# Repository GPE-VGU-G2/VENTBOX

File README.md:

# VENTBOX
Official documentation for the ventbox, maintained by Group 2_ GPE PROJECT (VGU_GPE25). This repository contains a technical description, an assembly guide, a Bill of Materials, as well as STEPs and STLs for the 3D printed parts.

VENTBOX is a smart storage solution that helps reduce food waste by actively controlling humidity inside food containers. Its thin, surface-mounted module can be added to existing Lock &amp; Lock lids without affecting the ability to stack containers in the refrigerator.

Ventbox is a module that mounts on the original lid of a 1.9 L Lock & Lock HPL818 food container (the lid only needs two holes, Ø12.3 and Ø10.3). It extracts moist air from the container to limit condensation while the container is kept in the refrigerator.
The module protrudes 8.0 mm above the lid surface and measures 92.8 × 43.3 × 7.5 mm. It is controlled by a Seeed XIAO nRF52840 with an SHT40 sensor; Sunon UB5U3-700 centrifugal blower fan; LP303035 LiPo battery.
Since rev 1.1 there is also a freshness timer: hold the button for 2 s when storing food, and the RGB LED on the module cover flashes green for 2 days, orange for 3 days, red for 2 days, then red double flashes once 7 days have passed. The timer runs independently of the fan and shares the XIAO, battery and button (firmware/README.md).

License

The license "CERN Open Hardware Licence Version 2 - Strongly Reciprocal" applies to all parts of the documentation in the repository.

Disclaimer

For Experienced Users Only
 This project is intended for individuals with sufficient knowledge and experience in handling electrical devices, components, and tools. Users are responsible for ensuring that any construction, modification, or operation is carried out safely and in accordance with applicable laws and regulations.

No Safety Guarantee
 The information provided is based on publicly available resources and is intended for educational and experimental purposes only. A self-built container/box does not replace a commercially manufactured and certified appliance. No representation, warranty, or guarantee is made regarding the safety, reliability, performance, or suitability of any device constructed using this information.

Use at Your Own Risk
 Any construction, modification, or use of a self-built container/box is undertaken entirely at your own risk. The author and contributors accept no responsibility or liability for any damage, injury, loss, malfunction, or other consequences resulting from the use of the information provided.

Not a Certified Product
 Any container/box built using this documentation is not a CE-certified product and has not been tested or approved under the standards applicable to commercial kitchen appliances or consumer products.

Prototype Status
 The self-built container/box should be considered a prototype or experimental device. It may not meet the safety, electrical, mechanical, food-contact, or regulatory requirements applicable to commercial products. Users are strongly advised to exercise caution and provide appropriate supervision during testing and operation.

Independent of Commercial Products
 This documentation is provided separately from any commercial products offered by the author and is intended solely for educational purposes. The purchase of any product from the author does not automatically grant rights to, include, or require the use of this documentation. Any use of the documentation is entirely independent of any product purchase.

Acceptance of Terms
 By accessing, using, or relying on the information provided, you acknowledge that you have read, understood, and agreed to this disclaimer. You assume full responsibility for the construction, operation, and use of any self-built container/box and do so entirely at your own risk.
How to start

Use the document "Technical documentation, BOM and Assembly Guide" to familiarise yourself with VENTBOX. The Bill of Materials included in the document contains the component names which are reused throughout the Github project.

Assembly_guide	  9-step illustrated assembly guide (ASSEMBLY\\\_GUIDE.md)
3D Model in step file/            STEP AP214/AP242 assembly + parts/\\\*.step,
DXF/       			 2D drawings dxf
3D-printed components/            STL files of the 3D-printed parts (base, module cover, 2 nuts, button, light pipe)
Electronics/
kicad/           ventbox.kicad_pro / .kicad_sch / .kicad_pcb / .kicad_sym / .net, ERC + DRC
kicad/fab/       gerbers + drill, component positions, PCB STEP, PCB layer PDF, render images
tools/           scripts that generate the schematic and PCB (fully reproducible)
Firmware/
ventbox/         ventbox.ino
build/           compiled .hex and DFU .zip package
Datasheets/        11 PDF datasheets
```

## Verification status (08 Nov 2026)

|Item|Result|
|-|-|
|3D model|Rev 1.1: housing split into module base + module cover, modelled threads, watertight STL; all solids valid, no interference between parts (`chk\\\\\\\\\\\\\\\_addon.py`); the lid only loses 303 mm³, exactly the volume of the 2 holes|
|Schematic|ERC: 0 errors, 0 warnings|
|PCB|Rev 1.2 (rev 1.1 added RGB LED D2, R3–R5, TP7–TP9): DRC 0 errors, 0 unconnected pads; the 17 `lib\\\\\\\\\\\\\\\_footprint\\\\\\\\\\\\\\\_mismatch` warnings are caused by intentionally moving footprint silkscreen to the Fab layer (the 16 × 16 mm board is too small)|
|Firmware|v1.2 (freshness timer since v1.1) compiles successfully for `Seeeduino:nrf52:xiaonRF52840`: 52 660 bytes (6 % flash)|
|Tested on real hardware|Not yet. When a prototype is available, re-measure the XIAO height, check the fan fit, and check the LED brightness and orange colour through the light pipe|

## Third-party software

The firmware `firmware/ventbox/ventbox.ino` is original Group 2 code. It uses these standard open-source libraries (not copied into the repo; installed via the Arduino Library/Boards Manager):

\* Wire (I2C), part of the \[Seeed nRF52 Arduino core](https://github.com/Seeed-Studio/Adafruit\_nRF52\_Arduino) – Arduino LLC / Sandeep Mistry / Adafruit, LGPL-2.1
\* \[Adafruit SHT4x Library](https://github.com/adafruit/Adafruit\_SHT4x) – Adafruit Industries, BSD
\* \[Adafruit BusIO](https://github.com/adafruit/Adafruit\_BusIO) – Adafruit Industries, MIT
\* \[Adafruit Unified Sensor](https://github.com/adafruit/Adafruit\_Sensor) – Adafruit Industries, Apache-2.0
\* \[Seeed nRF52 Boards core 1.1.13](https://github.com/Seeed-Studio/Adafruit\_nRF52\_Arduino) incl. \[Adafruit TinyUSB](https://github.com/adafruit/Adafruit\_TinyUSB\_Arduino) – Seeed Studio / Adafruit, LGPL-2.1 / MIT

Versions, purpose and licence of each library: \[firmware/README.md](firmware/README.md#third-party-libraries-and-origin).

## Licence

Hardware, documentation and firmware are released under the CERN Open Hardware Licence Version 2 – Strongly Reciprocal (CERN-OHL-S v2), the course default (KickOff p. 49 #10). The LICENSE file is added by the person responsible for checklist item 12.

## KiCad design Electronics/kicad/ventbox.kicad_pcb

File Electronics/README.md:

# Electronics – KiCad (checklist item 4)

KiCad 9 project in the `kicad/` folder: open `ventbox.kicad_pro` with KiCad 9.0 or later.

## Architecture

- **XIAO nRF52840 (U1):** reads the SHT40 (U2) over I2C on pins D4/D5, reads button SW1 on pin D1, switches fan M1 via pin D2, and drives RGB LED D2 (freshness timer) via pins D7/D8/D6.
- **16 × 16 mm sub-board:** connected to the blocks above with soldered wires, contains:
  - Q1 AO3400A, low-side switch for the fan;
  - R1 100 Ω in series with the Q1 gate, R2 10 kΩ gate pull-down to GND so the fan stays off while the XIAO boots;
  - D1 B5819W, fan flyback clamp;
  - button SW1;
  - common-anode RGB LED D2 XINGLIGHT XL-1615RGBC-RF (1.6 × 1.5 × 0.6 mm) with R3 330 Ω (red), R4 150 Ω (green), R5 150 Ω (blue), size 0402;
  - 9 wire solder pads (6 pads of 1.5 mm for power/fan/button, 3 pads of 1.0 mm for the LED).
- **Power:** the fan is powered directly from the battery (VBAT). The XIAO charges the battery from the USB-C port at 50 mA.

| Net | Connects |
|---|---|
| VBAT | BT1+, XIAO BAT+, TP4 (B+), TP5 (F+) → fan red wire, D1 cathode, D2 common anode (pin 2) |
| GND | BT1−, XIAO BAT− and GND, SHT40 GND, Q1 S, R2, SW1, TP3 (G) |
| FAN_PWM | XIAO D2 → TP2 (PW) → R1 |
| GATE | R1 → Q1 G, R2 |
| FAN_SW | Q1 D → TP6 (F−) → fan black wire, D1 anode |
| BTN | XIAO D1 → TP1 (BT) → SW1 |
| LED_R / LED_G / LED_B | XIAO D7 / D8 / D6 → TP7 / TP8 / TP9 → R3 / R4 / R5 → D2 pin 1 / 3 / 4 |
| +3V3, SDA, SCL | XIAO 3V3 / D4 / D5 → SHT40 VCC / SDA / SCL (direct wires) |

The pad labels (BT, PW, G, B+, F+, F−, R, G, B) are printed on the back of the board, directly behind each pad. The back silkscreen also carries "VENTBOX v1.2", "CERN-OHL-S" and "2026-11".

### Timer LED (rev 1.1)

- **Why a common anode tied to VBAT:** the LED lights when the GPIO pin is LOW. When the GPIO is HIGH (3.3 V), the voltage across the LED is only VBAT − 3.3 ≤ 0.9 V, lower than the minimum Vf of the red channel (1.8 V per the [XINGLIGHT datasheet](https://datasheet.lcsc.com/datasheet/pdf/0158170cd0ba772dd3d9a22a67a63b28.pdf?productCode=C965840)), so the LED is fully off.
- **LED current:** about 5–6 mA per channel at VBAT 3.8 V (limit 20 mA). The LED only flashes for 40 ms every 4 s, adding about 0.05 mA average current.
- **Custom footprint:** `kicad/ventbox.pretty/LED_RGB_XINGLIGHT_XL-1615RGBC.kicad_mod`, based on the land pattern on page 8 of the datasheet (pads 0.45 × 0.65; pin 1 R, 2 anode, 3 G, 4 B). The symbol is KiCad's built-in `Device:LED_RAGB`, with the same pin order.
- **Position:** D2 centre at (11.2, 10.0) on the sub-board, aligned with the light pipe VB-07.

## Files

| File | Content |
|---|---|
| `kicad/ventbox.kicad_sch` | Schematic (PDF version: `kicad/ventbox_schematic.pdf`) |
| `kicad/ventbox.kicad_pcb` | PCB 16 × 16 mm, 2 layers, FR-4 0.8 mm, GND copper zone on the top layer |
| `kicad/ventbox.net` | Netlist |
| `kicad/ventbox.kicad_sym`, `sym-lib-table` | Custom symbols: XIAO nRF52840, SHT40 breakout |
| `kicad/ventbox.pretty/`, `fp-lib-table` | Custom footprint: RGB LED XL-1615RGBC-RF |
| `kicad/erc.rpt`, `kicad/drc.rpt` | Check reports |
| `kicad/fab/gerber/` | Gerbers + Excellon drill files; zip them to order from JLCPCB |
| `kicad/fab/ventbox_pos.csv` | Component positions (pick & place) |
| `kicad/fab/ventbox_bom_kicad.csv` | BOM exported from KiCad |
| `kicad/fab/ventbox_pcb.step`, `ventbox_pcb_layers.pdf`, `renders/` | PCB STEP, PDF of each layer, 3D images of top/bottom side |

Check results (KiCad 9.0.8, 08 Nov 2026):
- **ERC:** 0 errors, 0 warnings.
- **DRC (with schematic parity check):** 0 errors, 0 unconnected pads, 0 parity issues.
  - 17 `lib_footprint_mismatch` warnings remain, caused by intentionally moving footprint silkscreen to the F.Fab layer because the board is so small.
- **Design rules:** track 0.3 mm, clearance 0.15 mm, via 0.6/0.3 mm, board-edge clearance 0.3 mm.

## Regenerating from the scripts

Requires KiCad 9 (`kicad-cli` and the bundled Python `pcbnew` module), Java 17 or later and [Freerouting 2.5.0](https://github.com/freerouting/freerouting/releases).

```bash
cd electronics/kicad
python3 ../tools/gen_schematic.py .                                       # schematic + library + _sch_meta.json
kicad-cli sch erc --severity-all -o erc.rpt ventbox.kicad_sch
kicad-cli sch export netlist -o ventbox.net ventbox.kicad_sch
/usr/bin/python3 ../tools/gen_pcb.py . freerouting-2.5.0.jar             # placement + autorouting
/usr/bin/python3 ../tools/fill_zones.py ventbox.kicad_pcb                 # GND copper pour
kicad-cli pcb drc --schematic-parity --severity-all -o drc.rpt ventbox.kicad_pcb
kicad-cli pcb export gerbers -l F.Cu,B.Cu,F.Paste,B.Paste,F.SilkS,B.SilkS,F.Mask,B.Mask,Edge.Cuts -o fab/gerber/ ventbox.kicad_pcb
kicad-cli pcb export drill -o fab/gerber/ --excellon-separate-th ventbox.kicad_pcb
kicad-cli pcb export pos --format csv --units mm --side both -o fab/ventbox_pos.csv ventbox.kicad_pcb
kicad-cli sch export pdf -o ventbox_schematic.pdf ventbox.kicad_sch
/usr/bin/python3 ../tools/dump_pcb_parts.py ventbox.kicad_pcb ../../mechanical/cad_native/pcb_parts.json
```

## Ordering the PCB

Zip the `fab/gerber/` folder and upload it to JLCPCB with these parameters:
- 2 layers, FR-4, 0.8 mm thick;
- size 16 × 16 mm, minimum track width and spacing 0.15 mm.

The SMD parts are 0603, 0402, SOT-23 and a 1615 LED.
- 0603 and SOT-23 can be hand-soldered.
- The 1615 LED and the 0402 resistors are very small: use solder paste + hot air, or order JLCPCB's assembly service (PCBA) with `fab/ventbox_pos.csv`.

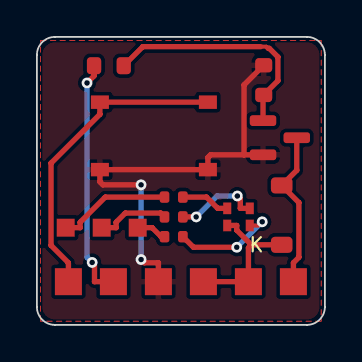
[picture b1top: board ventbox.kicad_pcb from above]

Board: 2 copper layers, 16.0 x 16.0 mm, 18 parts (0 on the bottom side), 12 nets.

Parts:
D1: B5819W; D_SOD-123
D2: XL-1615RGBC-RF; LED_RGB_XINGLIGHT_XL-1615RGBC
Q1: AO3400A; SOT-23
R1: 100; R_0603_1608Metric
R2: 10k; R_0603_1608Metric
R3: 330; R_0402_1005Metric
R4, R5: 150; R_0402_1005Metric
SW1: TS-1187A; SW_Push_1P1T_XKB_TS-1187A
TP1: BTN; TestPoint_Pad_1.5x1.5mm
TP2: PWM; TestPoint_Pad_1.5x1.5mm
TP3: GND; TestPoint_Pad_1.5x1.5mm
TP4: VBAT; TestPoint_Pad_1.5x1.5mm
TP5: FAN+; TestPoint_Pad_1.5x1.5mm
TP6: FAN-; TestPoint_Pad_1.5x1.5mm
TP7: LED_R; TestPoint_Pad_1.0x1.0mm
TP8: LED_G; TestPoint_Pad_1.0x1.0mm
TP9: LED_B; TestPoint_Pad_1.0x1.0mm

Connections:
/BTN: SW1.1, TP1.1
/FAN_PWM: R1.1, TP2.1
/FAN_SW: D1.2, Q1.3, TP6.1
/GATE: Q1.1, R1.2, R2.1
/GND: Q1.2, R2.2, SW1.2, TP3.1
/LED_B: R5.1, TP9.1
/LED_BK: D2.4, R5.2
/LED_G: R4.1, TP8.1
/LED_GK: D2.3, R4.2
/LED_R: R3.1, TP7.1
/LED_RK: D2.1, R3.2
/VBAT: D1.1, D2.2, TP4.1, TP5.1

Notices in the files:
Electronics/kicad/ventbox.kicad_pcb:
License: CERN-OHL-S-2.0
